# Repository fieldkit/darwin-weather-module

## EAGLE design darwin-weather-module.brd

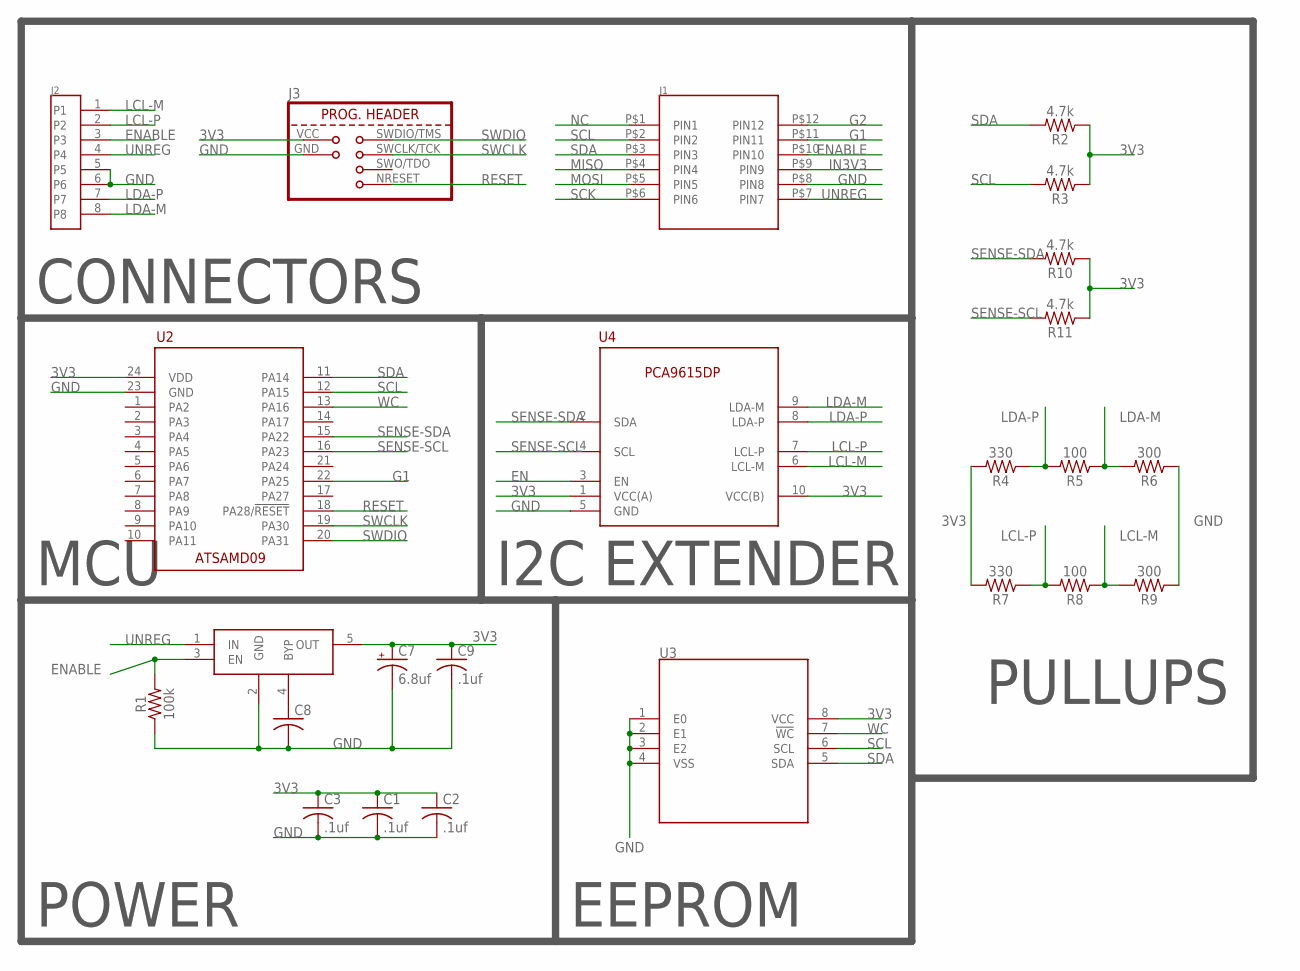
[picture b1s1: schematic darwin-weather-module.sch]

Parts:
C1, C2, C3, C9: .1uf; C0603K
C7: 6.8uf; A/3216-18R
C8: C-USC0603K; C0603K
J1: 2X6-HEADERS; M20-7810645
J2: 95501-6889VERT; 85513-5009
J3: TAG-CONNECT; TC2030-IDC
R1: 100k; 0603
R2, R3, R10, R11: 4.7k; 0603
R4, R7: 330; 0603
R5, R8: 100; 0603
R6, R9: 300; 0603
U2: ATSAMD09; QFN50P400X400X100-25T200
U3: M24C02-WMN6TP; SOIC127P600X175-8
U4: PCA9615; SOP50P490X110-10
U$4: MIC5219-3.3YM5-TR; SOT95P280X145-5

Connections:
3V3: C1.1, C2.1, C3.1, C7.+, C9.1, J3.VCC, R2.1, R3.1, R4.2, R7.2, R10.1, R11.1, U2.24 (VDD), U3.8 (VCC), U4.1 (VCC(A)), U4.10 (VCC(B)), U$4.5 (OUT)
EN: U4.3 (EN)
ENABLE: J1.P$10 (PIN10), J2.3, R1.2, U$4.3 (EN)
G1: J1.P$11 (PIN11), U2.22 (PA25)
G2: J1.P$12 (PIN12)
GND: C1.2, C2.2, C3.2, C7.-, C8.2, C9.2, J1.P$8 (PIN8), J2.5, J2.6, J3.GND, R1.1, R6.1, R9.1, U2.23 (GND), U3.1 (E0), U3.2 (E1), U3.3 (E2), U3.4 (VSS), U4.5 (GND), U$4.2 (GND)
IN3V3: J1.P$9 (PIN9)
LCL-M: J2.1, R8.1, R9.2, U4.6 (LCL-M)
LCL-P: J2.2, R7.1, R8.2, U4.7 (LCL-P)
LDA-M: J2.8, R5.1, R6.2, U4.9 (LDA-M)
LDA-P: J2.7, R4.1, R5.2, U4.8 (LDA-P)
MISO: J1.P$4 (PIN4)
MOSI: J1.P$5 (PIN5)
unnamed: C8.1, U$4.4 (BYP)
NC: J1.P$1 (PIN1)
RESET: J3.NRESET (RESET), U2.18 (PA28/!RESET)
SCK: J1.P$6 (PIN6)
SCL: J1.P$2 (PIN2), R3.2, U2.12 (PA15), U3.6 (SCL)
SDA: J1.P$3 (PIN3), R2.2, U2.11 (PA14), U3.5 (SDA)
SENSE-SCL: R11.2, U2.16 (PA23), U4.4 (SCL)
SENSE-SDA: R10.2, U2.15 (PA22), U4.2 (SDA)
SWCLK: J3.SWCLK/TCK (SWCLK), U2.19 (PA30)
SWDIO: J3.SWDIO/TMS (SWDIO), U2.20 (PA31)
UNREG: J1.P$7 (PIN7), J2.4, U$4.1 (IN)
WC: U2.13 (PA16), U3.7 (!WC)

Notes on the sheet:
CONNECTORS
MCU
I2C EXTENDER
POWER
EEPROM
PULLUPS

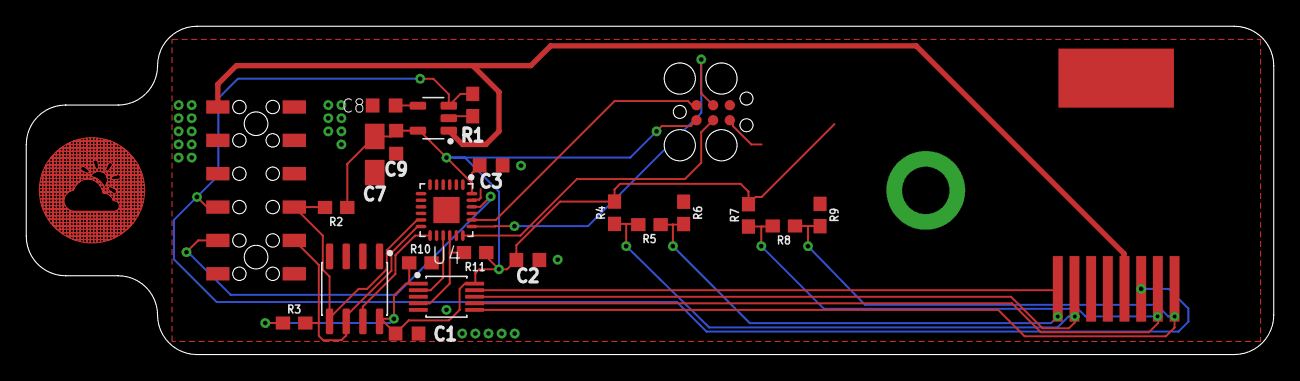
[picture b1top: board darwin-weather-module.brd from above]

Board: 2 copper layers, 95.0 x 25.0 mm, 24 parts (0 on the bottom side), 18 nets.

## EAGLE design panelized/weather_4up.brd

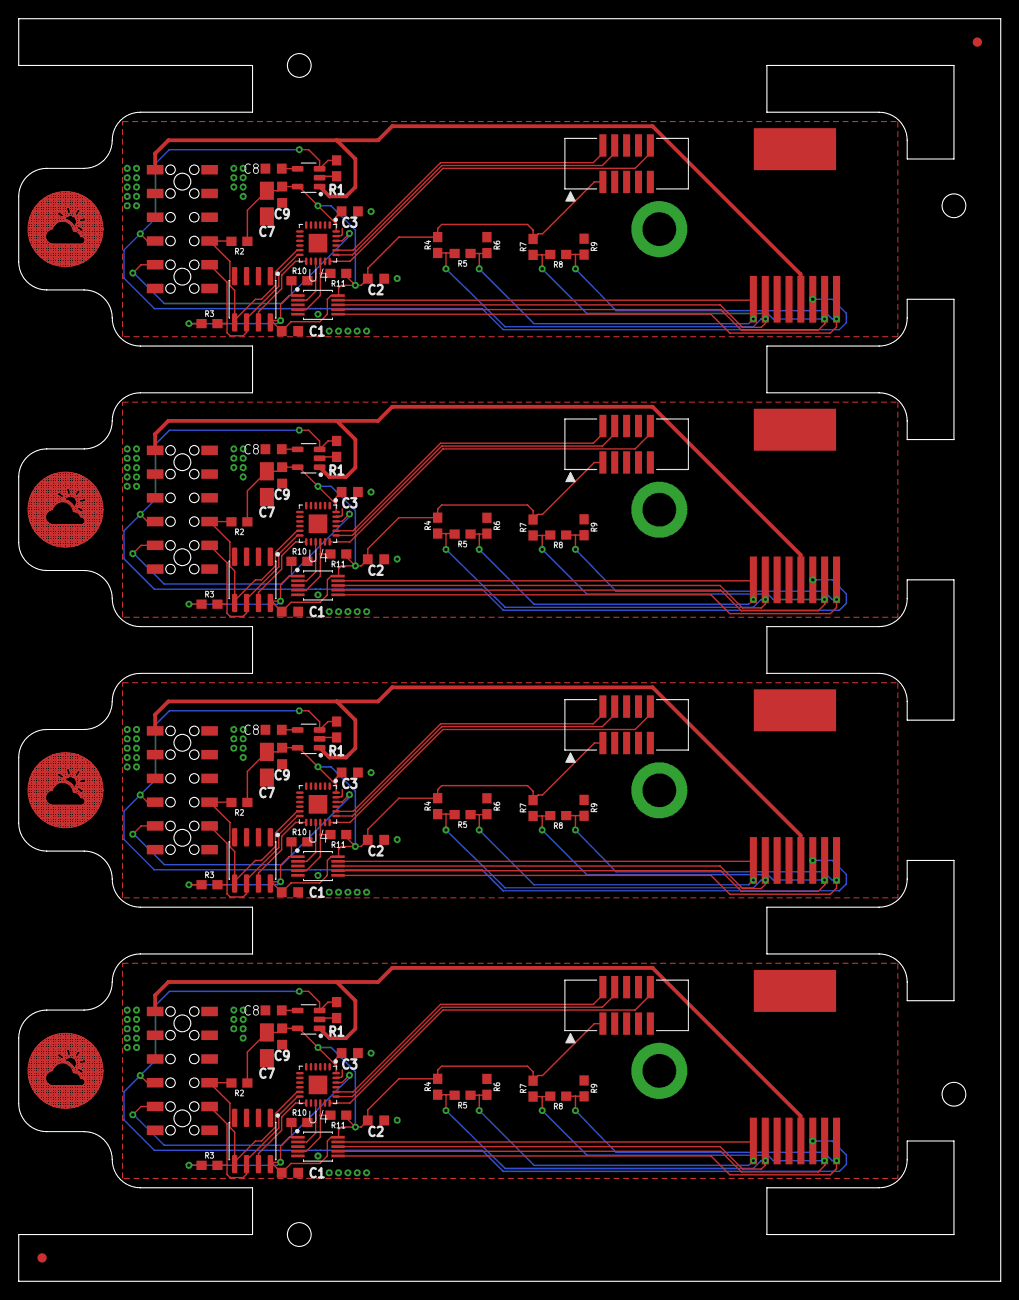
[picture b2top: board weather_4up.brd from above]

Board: 2 copper layers, 105.0 x 135.0 mm, 98 parts (0 on the bottom side), 72 nets.

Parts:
C1, C2, C3, C6, C9, C10, C11, C12, C15, C16, C17, C18, C21, C22, C23, C24: .1uf; C0603K
C4, C7, C13, C19: 6.8uf; A/3216-18R
C5, C8, C14, C20: C0603K
FID1, FID13: FIDUCIAL_1MM
J1, J3, J5, J7: 2X6-HEADERS; M20-7810645
J2, J4, J6, J8: 95501-6889VERT; 85513-5009
R1, R12, R23, R34: 100k; 0603
R2, R3, R10, R11, R13, R14, R21, R22, R24, R25, R32, R33, R35, R36, R43, R44: 4.7k; 0603
R4, R7, R15, R18, R26, R29, R37, R40: 330; 0603
R5, R8, R16, R19, R27, R30, R38, R41: 100; 0603
R6, R9, R17, R20, R28, R31, R39, R42: 300; 0603
U1, U2, U7, U10: ATSAMD09; QFN50P400X400X100-25T200
U3, U5, U8, U11: M24C02-WMN6TP; SOIC127P600X175-8
U4, U6, U9, U12: PCA9615; SOP50P490X110-10
U$1, U$2, U$3, U$4: MIC5219-3.3YM5-TR; SOT95P280X145-5
X1, X2, X3, X4: 2X05_1.27MM_BOX_NOPOSTS

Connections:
3V1: C4.+, C6.1, C10.1, C11.1, C12.1, R13.1, R14.1, R15.2, R18.2, R21.1, R22.1, U1.24, U5.8, U6.1, U6.10, U$1.5, X2.1
3V2: C13.+, C15.1, C16.1, C17.1, C18.1, R24.1, R25.1, R26.2, R29.2, R32.1, R33.1, U7.24, U8.8, U9.1, U9.10, U$2.5, X3.1
3V3: C1.1, C2.1, C3.1, C7.+, C9.1, R2.1, R3.1, R4.2, R7.2, R10.1, R11.1, U2.24, U3.8, U4.1, U4.10, U$4.5, X1.1
3V4: C19.+, C21.1, C22.1, C23.1, C24.1, R35.1, R36.1, R37.2, R40.2, R43.1, R44.1, U10.24, U11.8, U12.1, U12.10, U$3.5, X4.1
ENABLE: J1.P$10, J2.3, R1.2, U$4.3
ENABLE1: J3.P$10, J4.3, R12.2, U$1.3
ENABLE2: J5.P$10, J6.3, R23.2, U$2.3
ENABLE3: J7.P$10, J8.3, R34.2, U$3.3
G1: J1.P$11, U2.22
G3: J3.P$11, U1.22
G5: J5.P$11, U7.22
G7: J7.P$11, U10.22
GND: C1.2, C2.2, C3.2, C7.-, C8.2, C9.2, J1.P$8, J2.5, J2.6, R1.1, R6.1, R9.1, U2.23, U3.1, U3.2, U3.3, U3.4, U4.5, U$4.2, X1.3, X1.5, X1.9
GND2: C4.-, C5.2, C6.2, C10.2, C11.2, C12.2, J3.P$8, J4.5, J4.6, R12.1, R17.1, R20.1, U1.23, U5.1, U5.2, U5.3, U5.4, U6.5, U$1.2, X2.3, X2.5, X2.9
GND4: C13.-, C14.2, C15.2, C16.2, C17.2, C18.2, J5.P$8, J6.5, J6.6, R23.1, R28.1, R31.1, U7.23, U8.1, U8.2, U8.3, U8.4, U9.5, U$2.2, X3.3, X3.5, X3.9
GND6: C19.-, C20.2, C21.2, C22.2, C23.2, C24.2, J7.P$8, J8.5, J8.6, R34.1, R39.1, R42.1, U10.23, U11.1, U11.2, U11.3, U11.4, U12.5, U$3.2, X4.3, X4.5, X4.9
LCL-M: J2.1, R8.1, R9.2, U4.6
LCL-M1: J4.1, R19.1, R20.2, U6.6
LCL-M2: J6.1, R30.1, R31.2, U9.6
LCL-M3: J8.1, R41.1, R42.2, U12.6
LCL-P: J2.2, R7.1, R8.2, U4.7
LCL-P1: J4.2, R18.1, R19.2, U6.7
LCL-P2: J6.2, R29.1, R30.2, U9.7
LCL-P3: J8.2, R40.1, R41.2, U12.7
LDA-M: J2.8, R5.1, R6.2, U4.9
LDA-M1: J4.8, R16.1, R17.2, U6.9
LDA-M2: J6.8, R27.1, R28.2, U9.9
LDA-M3: J8.8, R38.1, R39.2, U12.9
LDA-P: J2.7, R4.1, R5.2, U4.8
LDA-P1: J4.7, R15.1, R16.2, U6.8
LDA-P2: J6.7, R26.1, R27.2, U9.8
LDA-P3: J8.7, R37.1, R38.2, U12.8
unnamed: C5.1, U$1.4
unnamed: C14.1, U$2.4
unnamed: C8.1, U$4.4
unnamed: C20.1, U$3.4
RESET: U2.18, X1.10
RESET1: U1.18, X2.10
RESET2: U7.18, X3.10
RESET3: U10.18, X4.10
SCL: J1.P$2, R3.2, U2.12, U3.6
SCL1: J3.P$2, R14.2, U1.12, U5.6
SCL2: J5.P$2, R25.2, U7.12, U8.6
SCL3: J7.P$2, R36.2, U10.12, U11.6
SDA: J1.P$3, R2.2, U2.11, U3.5
SDA1: J3.P$3, R13.2, U1.11, U5.5
SDA2: J5.P$3, R24.2, U7.11, U8.5
SDA3: J7.P$3, R35.2, U10.11, U11.5
SENSE-SCL: R11.2, U2.16, U4.4
SENSE-SCL1: R22.2, U1.16, U6.4
SENSE-SCL2: R33.2, U7.16, U9.4
SENSE-SCL3: R44.2, U10.16, U12.4
SENSE-SDA: R10.2, U2.15, U4.2
SENSE-SDA1: R21.2, U1.15, U6.2
SENSE-SDA2: R32.2, U7.15, U9.2
SENSE-SDA3: R43.2, U10.15, U12.2
SWCLK: U2.19, X1.4
SWCLK1: U1.19, X2.4
SWCLK2: U7.19, X3.4
SWCLK3: U10.19, X4.4
SWDIO: U2.20, X1.2
SWDIO1: U1.20, X2.2
SWDIO2: U7.20, X3.2
SWDIO3: U10.20, X4.2
UNREG: J1.P$7, J2.4, U$4.1
UNREG1: J3.P$7, J4.4, U$1.1
UNREG2: J5.P$7, J6.4, U$2.1
UNREG3: J7.P$7, J8.4, U$3.1
WC: U2.13, U3.7
WC1: U1.13, U5.7
WC2: U7.13, U8.7
WC3: U10.13, U11.7

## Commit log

2019-07-17 Test Article 1
2019-07-17 Schematic Cleanup
2019-07-17 Added I2C Pullups and GPIO connection to backplane. Removed deprecated module mounting hole.
2019-07-17 Fixed via overlap. TA2.
2019-08-22 Changed range extender to PCA9615
2019-10-09 Fixed pullups and mfg cleanup.
2019-10-17 Changed Power Architecture for Sensor/Module synchronization. TA3.
2020-01-16 New module footprint, icon, and relocated programming header.
2021-02-16 Migrated programming header to Tag-Connect.

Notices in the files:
parts and their libraries:
SparkFun-Resistors: Licensing: Creative Commons ShareAlike 4.0 International - https://creativecommons.org/licenses/by-sa/4.0
